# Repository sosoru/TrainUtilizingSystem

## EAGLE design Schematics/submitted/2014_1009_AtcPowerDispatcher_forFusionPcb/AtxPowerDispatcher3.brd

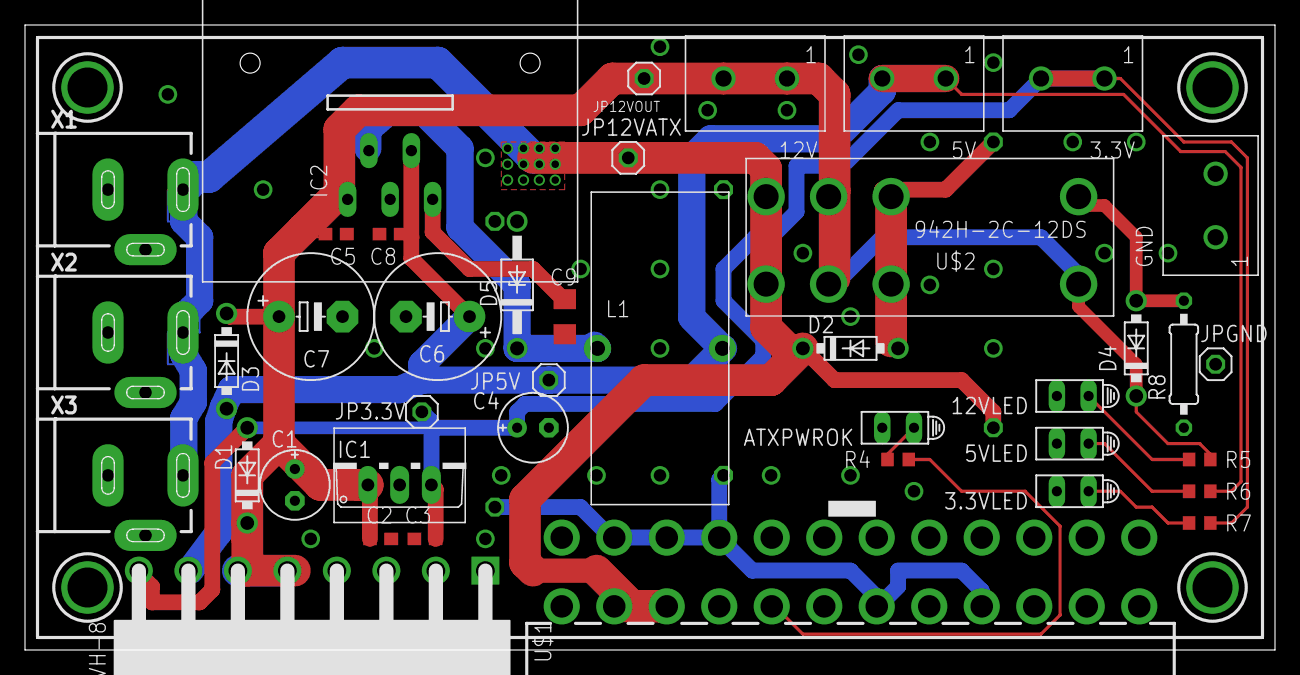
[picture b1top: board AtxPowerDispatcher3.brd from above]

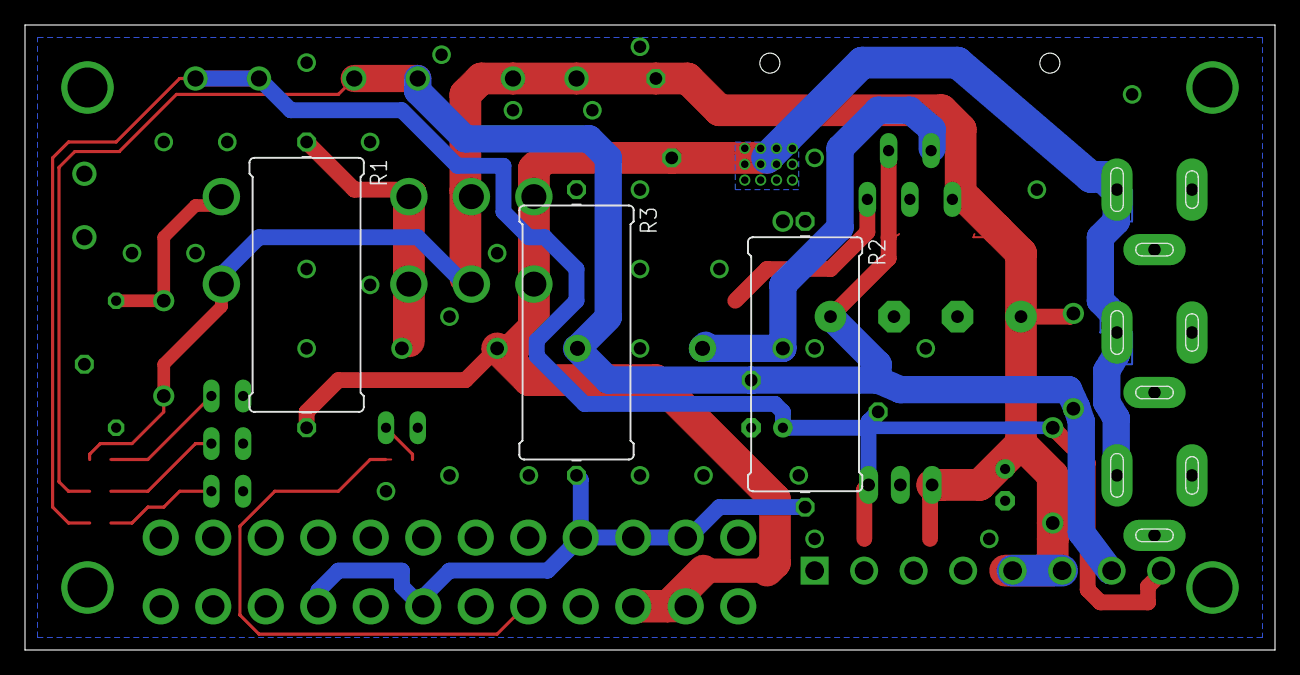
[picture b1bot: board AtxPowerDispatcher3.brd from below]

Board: 2 copper layers, 100.0 x 50.0 mm, 44 parts (3 on the bottom side), 15 nets.

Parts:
3.3V, 5V, 12V: 1X02_BIG
3.3VLED, 5VLED, 12VLED: HLMP6
ATXPWROK: HLMP6
C1: 33u; E2,5-6E
C2, C3, C5, C8: 0.1u; C0603
C4: 100u; E2,5-6E
C6, C7: 1000uF low-ESR; E5-10,5
C9: 10u; C1206
D1, D2, D3, D4: 1N5817-B; DO41-7.6
D5: 1N4728; DO41Z10
GND: 1X02_BIG
IC1: 788TV; TO220V
IC2: SI-8050; TO220-5
J1: ATX24RH; ATX24_RIGHT_ANGLE
JP3.3V, JP5V, JP12VATX, JP12VOUT: 1X01
JPGND: 1X01
L1: 47uH; 2200-12.7
R1: 30 5W; 0922/22
R2, R3: 5 5W; 0922/22
R4, R5, R6, R7: 1k; R0603
R8: 90ohm 1/4W; 0207/10
U$1: TUS_POWER_SOCKETVH-8; VH_8
U$2: 942H-2C-12DS; 942H
X1, X2, X3: DCJACK; 2DC-0005D100

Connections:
3.3V: 3.3V.P$1, 3.3V.P$2, C3.1, C4.+, D1.A, IC1.3, JP3.3V.1, R7.2, U$1.8
+5V: 5V.P$1, 5V.P$2, C7.+, C8.1, D3.A, IC2.4, JP5V.1, L1.2, R6.2, U$1.7
+12V: 12V.P$1, 12V.P$2, C1.+, C2.1, C5.1, C6.+, D1.C, D3.C, D4.C, IC1.1, IC2.1, JP12VOUT.1, R5.2, U$1.5, U$1.6, U$2.1, U$2.3, U$2.'3
GND: 3.3VLED.K, 5VLED.K, 12VLED.K, ATXPWROK.K, C1.-, C2.2, C3.2, C4.-, C5.2, C6.-, C7.-, C8.2, C9.2, D5.A, GND.P$1, GND.P$2, IC1.2, IC2.3, J1.3, J1.5, J1.7, J1.15, J1.16, J1.17, J1.18, J1.19, J1.24, JPGND.1, R2.1, R3.1, R8.1, U$1.1, U$1.2, U$1.3, U$1.4, X1.2, X1.3, X2.2, X2.3, X3.2, X3.3
unnamed: 12VLED.A, R5.1
unnamed: J1.8, R4.2
unnamed: J1.4, J1.6, J1.21, J1.22, J1.23, R2.2, R3.2
unnamed: 5VLED.A, R6.1
unnamed: 3.3VLED.A, R7.1
unnamed: ATXPWROK.A, R4.1
unnamed: D4.A, R8.2, U$2.'1
unnamed: D5.C, IC2.2, L1.1
unnamed: D2.A, R1.1, U$2.2, U$2.'2
unnamed: D2.C, J1.10, J1.11, JP12VATX.1, R1.2, U$2.4, U$2.'4, X1.1, X2.1, X3.1
unnamed: C9.1, IC2.5

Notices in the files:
parts and their libraries:
SparkFun: Licensing: CC v3.0 Share-Alike You are welcome to use this library for commercial purposes.
